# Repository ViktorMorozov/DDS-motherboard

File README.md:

# DDS-motherboard

A small motherboard to host a DDS AD9850, an Arduino Pro Clone and and an LCD. The project is composed of:
- Code to control the oscillation frequency through an AB encoder and display it in the LCD.
- KICad project with schematics and PCB design
- Milling file (G code) for CNC1610 and 0.1mm mill

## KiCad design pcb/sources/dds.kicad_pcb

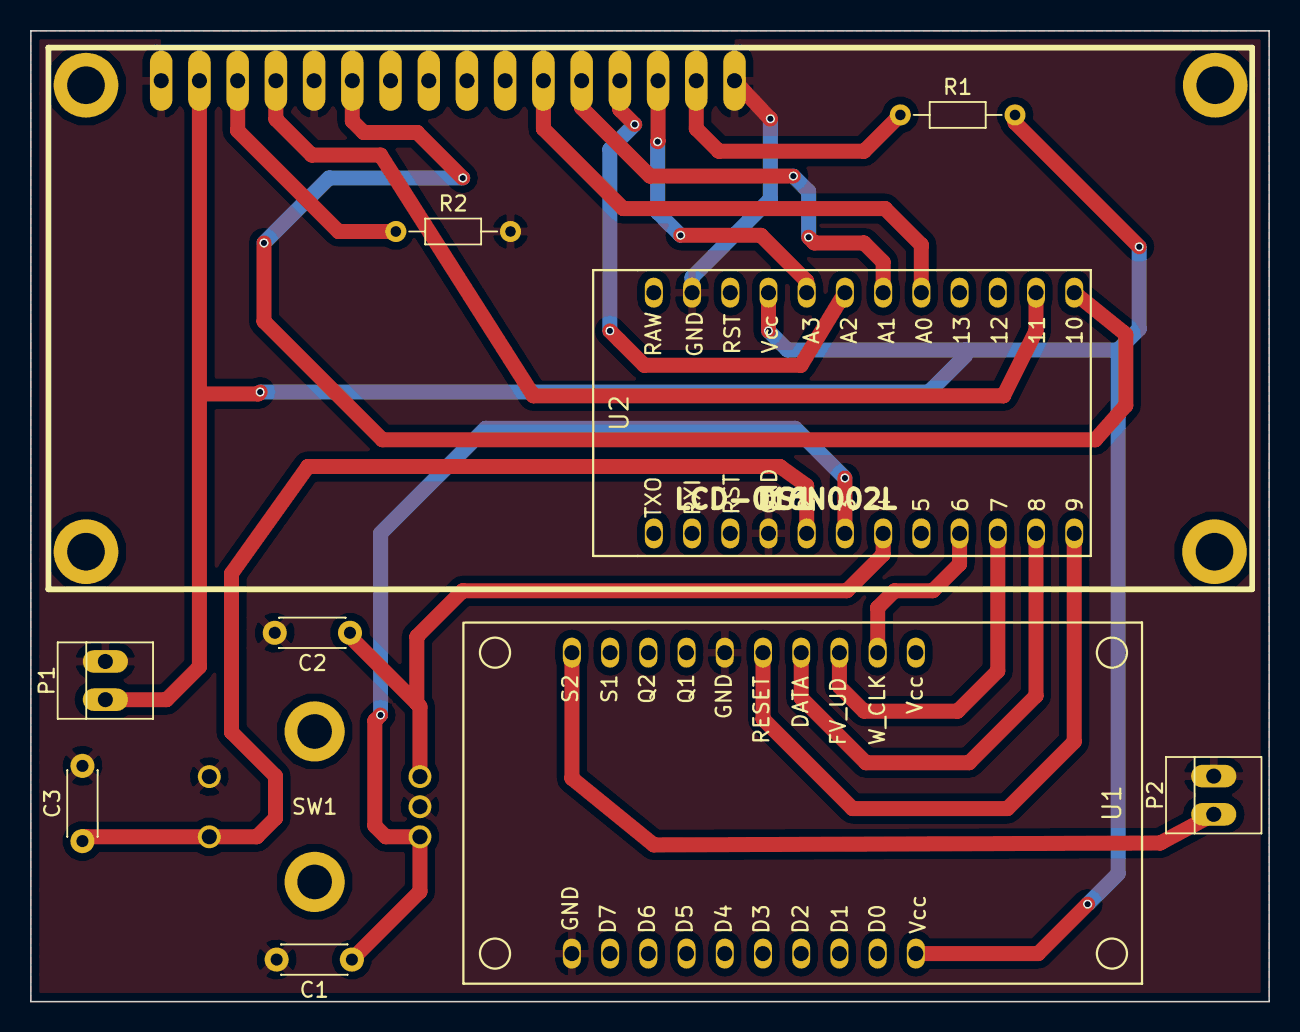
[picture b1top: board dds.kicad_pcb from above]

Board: 2 copper layers, 82.3 x 64.5 mm, 11 parts (0 on the bottom side), 18 nets.

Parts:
C1, C2, C3: C; C_Disc_D4.3mm_W1.9mm_P5.00mm
DS1: LCD-016N002L; LCD-16x2
P1, P2: CONN_01X02; PINHEAD1-2
R1, R2: R; R_Axial_DIN0204_L3.6mm_D1.6mm_P7.62mm_Horizontal
SW1: Control; Encoder_PEC11-4215F-S00
U1: AD9850_BreakOut; AD9850_BreakoutBoard
U2: ArduinoProClone; ArduinoPro_Mini

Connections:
5V: DS1.2, P1.1, R1.2, U1.1, U1.11, U2.21
A: C1.1, SW1.1, U2.6
B: C2.1, SW1.3, U2.7
GND: C1.2, C2.2, C3.2, DS1.1, DS1.5, DS1.16, P1.2, P2.2, R2.2, SW1.2, SW1.5, U1.10, U1.16, U2.4, U2.23
unnamed: DS1.3, R2.1
unnamed: DS1.4, U2.14
unnamed: DS1.6, U2.13
unnamed: DS1.11, U2.17
unnamed: DS1.12, U2.18
unnamed: DS1.13, U2.19
unnamed: DS1.14, U2.20
unnamed: DS1.15, R1.1
unnamed: U1.12, U2.9
unnamed: U1.13, U2.10
unnamed: U1.14, U2.11
unnamed: U1.15, U2.12
Pushbutton: C3.1, SW1.4, U2.5
SignalOut: P2.1, U1.20

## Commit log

2017-02-13 :octocat: Added .gitattributes & .gitignore files
2017-02-13 Added schematics and pcb design files
2017-02-13 Added initial version of the arduino firmware
2017-02-14 Gerber files for front layer and drill map.
2017-02-14 Gerber files moved and milling file created
2017-02-14 PDFs with schematics generated and files moved under sources folder
2017-02-14 Files moved to production and sources folder
2017-02-15 Added AD9850 library from f4go
2017-02-15 Minor tracks re-route in front layer
2017-02-25 First milling attempt
    First milling attempt
2017-02-25 New production code with 0.1 mm cut depth
2017-02-25 Gerbers used to generate the G code
2017-02-25 PDFs updated
